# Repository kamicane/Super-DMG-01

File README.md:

# Super DMG-01

A [KiCad](https://www.kicad.org/) 6.0 recreation of the original Game Boy, with a few modern twists.

One of the main goals of this project is to build an entire DMG using only a DMG CPU or a SGB CPU.

## Credits

- bit9 for the [DMG schematics](https://imgur.com/a/X5qKI) and [board scans](https://chipmusic.org/forums/post/215957/#p215957)
- [Gekkio](https://github.com/Gekkio) for the CPU, RAM, CART symbols from [Gekkio KiCad libs](https://github.com/Gekkio/gekkio-kicad-libs)
- [Wesk](https://bitbuilt.net/forums/index.php?members/wesk.1486/) for [these amazing DMG shell scans](https://bitbuilt.net/forums/index.php?threads/dmg-gameboy-scan.4479/), which allow me to do all sort of adapters and covers and whatnot, and test the pcb fitment virtually

## Boards

Like an original DMG, the Super DMG-01 is made out of separate boards. Doumentation for each board can be found in the relative sub-folders:

- CPU Board: [Super DMG CPU](super-dmg-cpu)
- JACK Board: [Super DMG JACK](super-dmg-jack)

## 3rd party boards

To complete the game boy additional boards are required:

- DC CONV Board: use [MouseBiteLabs](https://github.com/MouseBiteLabs)' [DMGC-PWR-01](https://github.com/MouseBiteLabs/Game-Boy-DMG-Color/tree/main/DMGC-PWR-01) or use one from a DMG
- LCD Board: Use any of the available IPS kits or use one from a DMG

## Disclaimer

I am not an electronics expert. Super DMG-01 might fry your games, set your house on fire and kill your pets.

## License

This work is licensed under the [Creative Commons Attribution-ShareAlike 4.0 International License.](http://creativecommons.org/licenses/by-sa/4.0/)

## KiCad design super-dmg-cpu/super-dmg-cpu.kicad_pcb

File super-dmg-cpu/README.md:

# Super DMG CPU

Super DMG CPU works with both IPS and DOT MATRIX LCD boards.

## Credits

The schematic is largely based on [the work done by bit 9](https://imgur.com/a/X5qKI).

I used [Gekkio KiCAD libs](https://github.com/Gekkio/gekkio-kicad-libs) for a few symbols (cpu, ram, cart connector, link port). The specialized footprints were traced by me using fusion 360, using these [scans by bit 9](https://chipmusic.org/forums/topic/13608/dmg-main-board-schematic-circuit-arduinoboy/) as a reference.

## Warning

v1.8 and below have an error with the Link Port, where the footprint was flipped (sigh). If you have a v1.8 or below please don't use the link port, as it might damage the other Game Boy! This was fixed in later versions.

## Features

### Compatibility

Super DMG CPU can be built using new components, except for the CPU, power switch and link connector. It is also possible to use some components harvested from a DMG.

### USB Type-C

The round power connector is replaced with an USB Type-C port. The port is only connected to a pad on the motherboard, you need to add your own battery charger and/or power regulator if you want to make use of it. This port is optional.

### Power distribution IC

A power distribution IC takes the system load away from the power switch, so the game boy remains fully operational even if the switch is not in an optimal condition. This circuit can be bypassed with a jumper.

### Internal ProSound

The headphone output does not pass through the amplifier, only the volume potentiometer.

## BOM

| Designator | Package | Qty | Value / Description | Source |
|------------|---------|-----|---------------------|--------|
| U1 | QFP-80 14x20 p0.8 | 1 | CPU | DMG, SGB
| U2 | SOP-28 17.5x8.4 p1.27 | 1 | VRAM | DMG, SGB, [LCSC](https://lcsc.com/product-detail/C1351073.html)
| U3 | SOP-28 17.5x8.4 p1.27 | 1 | RAM | DMG, SGB, [LCSC](https://lcsc.com/product-detail/C1351073.html)
| U4 | SSOP-18 6x7.4 p0.8 | 1 | Audio Amplifier | DMG
| EXT1 | | 1 | Link Connector | DMG
| DA1, DA2, DA3, DA4 | SOT-23-3 | 4 | BAV99-7-F | [LCSC](https://www.lcsc.com/product-detail/C106919.html)
| C1, C23 | 3528 | 2 | 100µf tantalum | [LCSC](https://lcsc.com/product-detail/C122271.html)
| SW1 | | 1 | Power Switch | DMG
| U5 | SOT-23-5 | 1 | Power Distribution | [LCSC](https://lcsc.com/product-detail/C517266.html)
| D2 | SOD-123 | 1 | 1N414 | [LCSC](https://lcsc.com/product-detail/C83528.html)
| X1 | HC-49S | 1 | 4.194304 MHz | DMG, [LCSC (TH)](https://lcsc.com/product-detail/C718646.html), [LCSC (SMD)](https://lcsc.com/product-detail/C2149317.html)
| USB1 | USB_C_16p | 1 | Charge Connector | [LCSC](https://lcsc.com/product-detail/C2931472.html)
| VR1 | | 1 | Volume Pot | DMG, [AliExpress](https://www.aliexpress.com/item/32840044311.html)
| CN1 | 1.25 x 21 SMD | 1 | LCD Board Connector | DMG, [AliExpress](https://www.aliexpress.com/item/1005005484837763.html)
| CN2 |  | 1 | Cart Connector | DMG, [AliExpress](https://www.aliexpress.com/item/1005002719771295.html)
| CN3 | | 1 | AA Battery Contacts | DMG, [AliExpress](https://www.aliexpress.com/item/32801068366.html)
| CN4 | 1.25 TH | 1 | Lipo Battery Connector | [LCSC](https://www.lcsc.com/product-detail/C722595.html)
| C3, C4 | 0805 | 2 | 1µF |
| C5, C6 | 0805 | 2 | 10µF |
| C7, C8, C9 | 0805 | 3 | 47nF |
| C10, C24, C25 | 0805 | 3 | 100nF |
| C12, C13, C14 | 0805 | 3 | 10nF |
| C16, C17, C18, C19 | 0805| 4 | 100pF |
| C21, C22 | 0805 | 2 | 27pF |
| R1, R2, R3, R4 | 0805 | 4 | 220Ω|
| R5, R6 | 0805 | 2 | 510Ω |
| R7 | 0805 | 1 | 180kΩ |
| R8 | 0805 | 1 | 1MΩ |
| R9 | 0805 | 1 | 10kΩ |
| R10, R11 | 0805 | 2 | 5.1kΩ |

## Assembly

- Solder all SMD components on the front side
- If using a power board with integrated power distribution close ```J5``` and do not install ```U5```, ```C24```, ```C25```, ```R9```
- If using an external amplifier, such as [Super DMG JACK](../super-dmg-jack) do not install ```U4```, ```C5-C9```, ```C23```
- If you do not need link functionality you can omit ```EXT1```, ```DA1-DA4```, ```R1-R4```, ```C16-C19```, ```D2```
- Solder the through hole components and the LCD board connector
- (Optional) solder the usb connector and cut an opening for the usb port in the front shell using the provided [rudimentary jig](../3d_models/dmg_usbc_jig.stl)
- The original DC jack hole can be covered with this simple [3d printed plug](../3d_models/dmg_dc_plug.stl)

## Notes

If using an original LCD board you need an original *DMG DC CONV* voltage regulator, as acceptable modern replacements that also include the -18v rail *do not exist yet*.

This pcb cannot be easily biverted yet.

## Ordering

Make sure you order with 1.0mm thickness.

## License

This work is licensed under the [Creative Commons Attribution-ShareAlike 4.0 International License.](http://creativecommons.org/licenses/by-sa/4.0/)

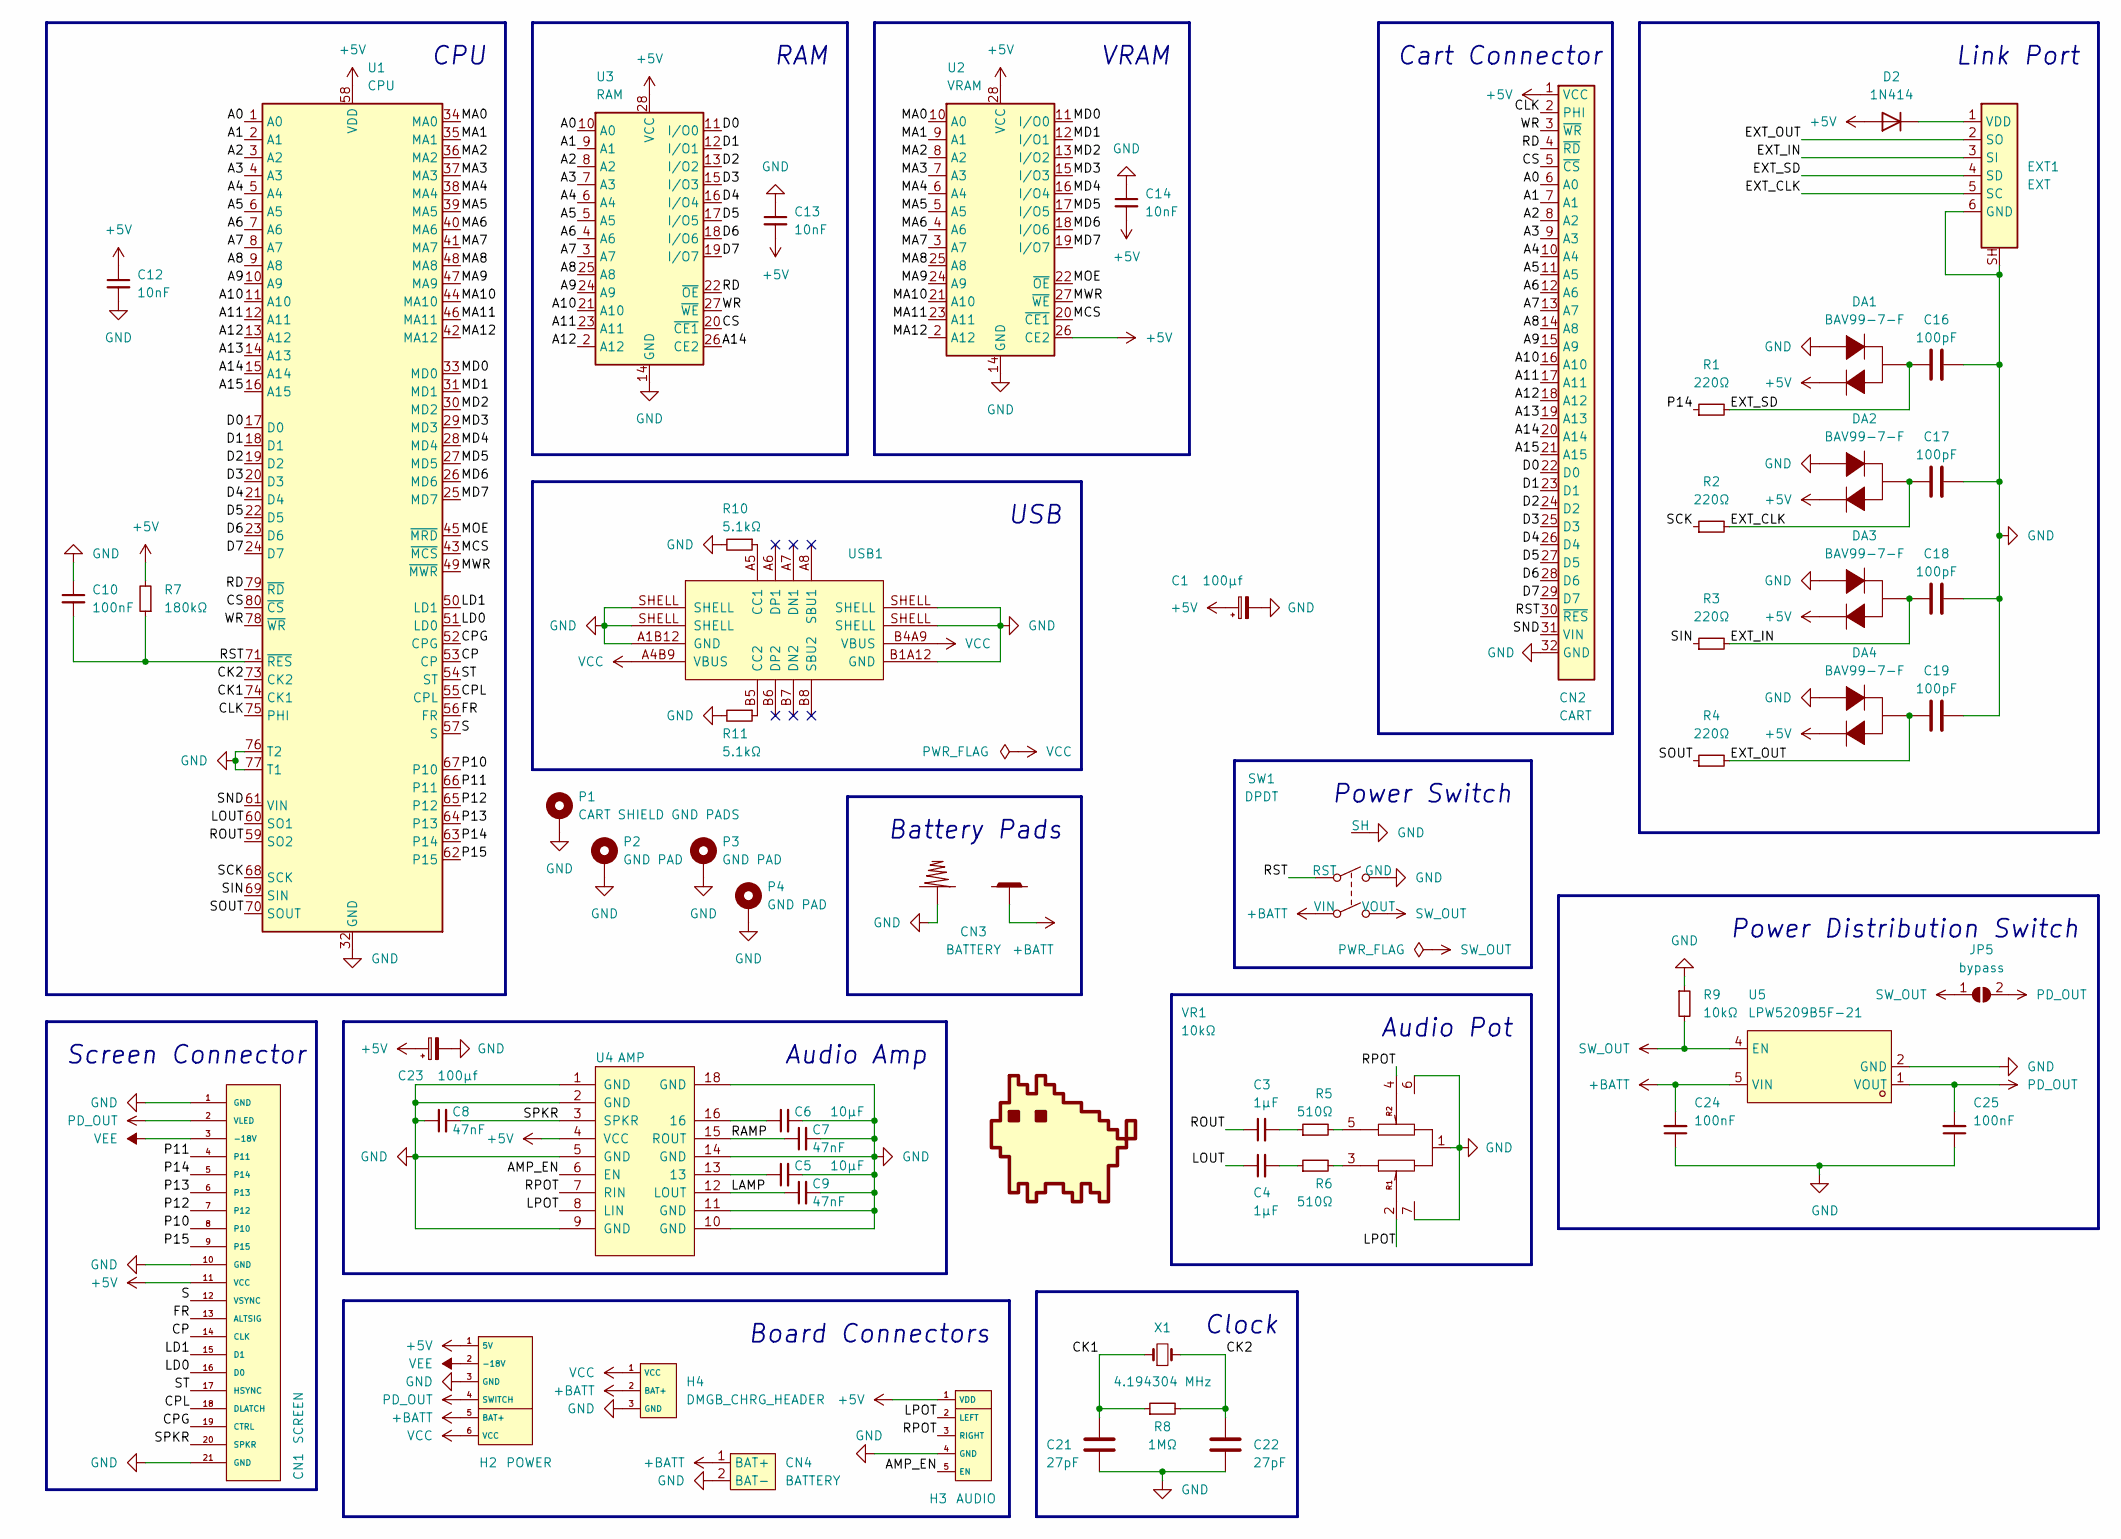
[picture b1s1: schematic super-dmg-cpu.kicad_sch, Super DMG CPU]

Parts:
C1, C23: 100µf; CP_EIA-3528-12_Kemet-T_Pad1.50x2.35mm_HandSolder; LCSC C122271
C3, C4: 1µF; C_0805_2012Metric_Pad1.18x1.45mm_HandSolder; LCSC C28323
C5, C6: 10µF; C_0805_2012Metric_Pad1.18x1.45mm_HandSolder; LCSC C15850
C7, C8, C9: 47nF; C_0805_2012Metric_Pad1.18x1.45mm_HandSolder; LCSC C53134
C10, C24, C25: 100nF; C_0805_2012Metric_Pad1.18x1.45mm_HandSolder; LCSC C49678
C12, C13, C14: 10nF; C_0805_2012Metric_Pad1.18x1.45mm_HandSolder; LCSC C1710
C16, C17, C18, C19: 100pF; C_0805_2012Metric_Pad1.18x1.45mm_HandSolder; LCSC C1790
C21, C22: 27pF; C_0805_2012Metric_Pad1.18x1.45mm_HandSolder; LCSC C527182
CN1: SCREEN; DMG_FPC_CONN
CN2: CART; DMG_CART_CONN
CN3: BATTERY; DMG_BATTERY_PADS
CN4: BATTERY; CONN-TH_2P-P1.25_HCTL_HC-1.25-2AW; LCSC C2845535
D2: 1N414; D_SOD-123; LCSC C83528
DA1, DA2, DA3, DA4: BAV99-7-F; SOT-23-3_L2.9-W1.3-P1.90-LS2.4-BR; LCSC C106919
EXT1: EXT; DMG_LINK_CONN
G1: kmc; kmc_6mm
H2: POWER; PAD_2.54_HYBRID_X6
H3: AUDIO; PAD_2.54_HYBRID_X5
H4: DMGB_CHRG_HEADER; PAD_2.54_HYBRID_X3
JP5: bypass; solder_jumper_x2
P1: CART SHIELD GND PADS; DMG_CART_SHIELD_CONTACT
P2, P3, P4: GND PAD; DMG_GROUNDPAD
R1, R2, R3, R4: 220Ω; R_0805_2012Metric_Pad1.20x1.40mm_HandSolder; LCSC C17557
R5, R6: 510Ω; R_0805_2012Metric_Pad1.20x1.40mm_HandSolder; LCSC C17734
R7: 180kΩ; R_0805_2012Metric_Pad1.20x1.40mm_HandSolder; LCSC C17501
R8: 1MΩ; R_0805_2012Metric_Pad1.20x1.40mm_HandSolder; LCSC C17514
R9: 10kΩ; R_0805_2012Metric_Pad1.20x1.40mm_HandSolder; LCSC C17414
R10, R11: 5.1kΩ; R_0805_2012Metric_Pad1.20x1.40mm_HandSolder; LCSC C27834
SW1: DPDT; DMGB_POWER_SWITCH; LCSC C2848866
U1: CPU; DMG_CPU
U2: VRAM; DMG_RAM_64K
U3: RAM; DMG_RAM_64K
U4: AMP; DMG_AMP
U5: LPW5209B5F-21; SOT-23-5_L2.9-W1.6-P0.95-LS2.8-BL; JLC Part Extended Part
USB1: CHARGE_PORT; USB_C_16p; LCSC C319148
VR1: 10kΩ; DMG_VOLUME_POT
X1: 4.194304 MHz; HC-49S; LCSC C2149317

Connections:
+5V: C1.1, C12.1, C13.2, C14.2, C23.1, CN1.11 (VCC), CN2.1 (VCC), D2.2 (A), DA1.2 (K), DA2.2 (K), DA3.2 (K), DA4.2 (K), H2.1 (5V), H3.1 (VDD), R7.2, U1.58 (VDD), U2.26 (CE2), U2.28 (VCC), U3.28 (VCC), U4.4 (VCC)
+BATT: C24.2, CN3.1 (+), CN4.1 (BAT+), H2.5 (BAT+), H4.2 (BAT+), SW1.2 (VIN), U5.5 (VIN)
/A0: CN2.6 (A0), U1.1 (A0), U3.10 (A0)
/A1: CN2.7 (A1), U1.2 (A1), U3.9 (A1)
/A2: CN2.8 (A2), U1.3 (A2), U3.8 (A2)
/A3: CN2.9 (A3), U1.4 (A3), U3.7 (A3)
/A4: CN2.10 (A4), U1.5 (A4), U3.6 (A4)
/A5: CN2.11 (A5), U1.6 (A5), U3.5 (A5)
/A6: CN2.12 (A6), U1.7 (A6), U3.4 (A6)
/A7: CN2.13 (A7), U1.8 (A7), U3.3 (A7)
/A8: CN2.14 (A8), U1.9 (A8), U3.25 (A8)
/A9: CN2.15 (A9), U1.10 (A9), U3.24 (A9)
/A10: CN2.16 (A10), U1.11 (A10), U3.21 (A10)
/A11: CN2.17 (A11), U1.12 (A11), U3.23 (A11)
/A12: CN2.18 (A12), U1.13 (A12), U3.2 (A12)
/A13: CN2.19 (A13), U1.14 (A13)
/A14: CN2.20 (A14), U1.15 (A14), U3.26 (CE2)
/A15: CN2.21 (A15), U1.16 (A15)
/AMP_EN: H3.5 (EN), U4.6 (EN)
/CK1: C21.2, R8.1, U1.74 (CK1), X1.1
/CK2: C22.2, R8.2, U1.73 (CK2), X1.2
/CLK: CN2.2 (PHI), U1.75 (PHI)
/CP: CN1.14 (CLK), U1.53 (CP)
/CPG: CN1.19 (CTRL), U1.52 (CPG)
/CPL: CN1.18 (DLATCH), U1.55 (CPL)
/CS: CN2.5 (~CS), U1.80 (~CS), U3.20 (~CE1)
/D0: CN2.22 (D0), U1.17 (D0), U3.11 (I/O0)
/D1: CN2.23 (D1), U1.18 (D1), U3.12 (I/O1)
/D2: CN2.24 (D2), U1.19 (D2), U3.13 (I/O2)
/D3: CN2.25 (D3), U1.20 (D3), U3.15 (I/O3)
/D4: CN2.26 (D4), U1.21 (D4), U3.16 (I/O4)
/D5: CN2.27 (D5), U1.22 (D5), U3.17 (I/O5)
/D6: CN2.28 (D6), U1.23 (D6), U3.18 (I/O6)
/D7: CN2.29 (D7), U1.24 (D7), U3.19 (I/O7)
/EXT_CLK: C17.1, DA2.3 (K), EXT1.5 (SC), R2.2
/EXT_IN: C18.1, DA3.3 (K), EXT1.3 (SI), R3.2
/EXT_OUT: C19.1, DA4.3 (K), EXT1.2 (SO), R4.2
/EXT_SD: C16.1, DA1.3 (K), EXT1.4 (SD), R1.2
/FR: CN1.13 (ALTSIG), U1.56 (FR)
/LAMP: C9.1, U4.12 (LOUT)
/LD0: CN1.16 (D0), U1.51 (LD0)
/LD1: CN1.15 (D1), U1.50 (LD1)
/LOUT: C4.1, U1.60 (SO1)
/LPOT: H3.2 (LEFT), U4.8 (LIN), VR1.2
/MA0: U1.34 (MA0), U2.10 (A0)
/MA1: U1.35 (MA1), U2.9 (A1)
/MA2: U1.36 (MA2), U2.8 (A2)
/MA3: U1.37 (MA3), U2.7 (A3)
/MA4: U1.38 (MA4), U2.6 (A4)
/MA5: U1.39 (MA5), U2.5 (A5)
/MA6: U1.40 (MA6), U2.4 (A6)
/MA7: U1.41 (MA7), U2.3 (A7)
/MA8: U1.48 (MA8), U2.25 (A8)
/MA9: U1.47 (MA9), U2.24 (A9)
/MA10: U1.44 (MA10), U2.21 (A10)
/MA11: U1.46 (MA11), U2.23 (A11)
/MA12: U1.42 (MA12), U2.2 (A12)
/MCS: U1.43 (~MCS), U2.20 (~CE1)
/MD0: U1.33 (MD0), U2.11 (I/O0)
/MD1: U1.31 (MD1), U2.12 (I/O1)
/MD2: U1.30 (MD2), U2.13 (I/O2)
/MD3: U1.29 (MD3), U2.15 (I/O3)
/MD4: U1.28 (MD4), U2.16 (I/O4)
/MD5: U1.27 (MD5), U2.17 (I/O5)
/MD6: U1.26 (MD6), U2.18 (I/O6)
/MD7: U1.25 (MD7), U2.19 (I/O7)
/MOE: U1.45 (~MRD), U2.22 (~OE)
/MWR: U1.49 (~MWR), U2.27 (~WE)
/P10: CN1.8 (P10), U1.67 (P10)
/P11: CN1.4 (P11), U1.66 (P11)
/P12: CN1.7 (P12), U1.65 (P12)
/P13: CN1.6 (P13), U1.64 (P13)
/P14: CN1.5 (P14), R1.1, U1.63 (P14)
/P15: CN1.9 (P15), U1.62 (P15)
/RAMP: C7.1, U4.15 (ROUT)
/RD: CN2.4 (~RD), U1.79 (~RD), U3.22 (~OE)
/ROUT: C3.1, U1.59 (SO2)
/RPOT: H3.3 (RIGHT), U4.7 (RIN), VR1.4
/RST: C10.2, CN2.30 (~RES), R7.1, SW1.5 (RST), U1.71 (~RES)
/S: CN1.12 (VSYNC), U1.57 (S)
/SCK: R2.1, U1.68 (SCK)
/SIN: R3.1, U1.69 (SIN)
/SND: CN2.31 (VIN), U1.61 (VIN)
/SOUT: R4.1, U1.70 (SOUT)
/SPKR: C8.2, CN1.20 (SPKR), U4.3 (SPKR)
/ST: CN1.17 (HSYNC), U1.54 (ST)
/WR: CN2.3 (~WR), U1.78 (~WR), U3.27 (~WE)
GND: C1.2, C5.2, C6.2, C7.2, C8.1, C9.2, C10.1, C12.2, C13.1, C14.1, C16.2, C17.2, C18.2, C19.2, C21.1, C22.1, C23.2, C24.1, C25.1, CN1.1 (GND), CN1.10 (GND), CN1.21 (GND), CN2.32 (GND), CN3.2 (-), CN4.2 (BAT-), DA1.1 (A), DA2.1 (A), DA3.1 (A), DA4.1 (A), EXT1.6 (GND), EXT1.SH, H2.3 (GND), H3.4 (GND), H4.3 (GND), P1.1, P2.1, P3.1, P4.1, R9.1, R10.2, R11.2, SW1.6 (GND), SW1.7 (SH), U1.32 (GND), U1.72 (GND), U1.76 (T2), U1.77 (T1), U2.14 (GND), U3.14 (GND), U4.1 (GND), U4.2 (GND), U4.5 (GND), U4.9 (GND), U4.10 (GND), U4.11 (GND), U4.14 (GND), U4.18 (GND), U5.2 (GND), USB1.A1B12 (GND), USB1.B1A12 (GND), USB1.SHELL, VR1.1, VR1.6 (EH), VR1.7 (EH)
unnamed: C3.2, R5.1
unnamed: C4.2, R6.1
unnamed: C5.1, U4.13
unnamed: C6.1, U4.16
unnamed: D2.1 (K), EXT1.1 (VDD)
unnamed: R5.2, VR1.5
unnamed: R6.2, VR1.3
unnamed: R10.1, USB1.A5 (CC1)
unnamed: R11.1, USB1.B5 (CC2)
PD_OUT: C25.2, CN1.2 (VLED), H2.4 (SWITCH), JP5.2 (B), U5.1 (VOUT)
SW_OUT: JP5.1 (A), R9.2, SW1.1 (VOUT), U5.4 (EN)
VCC: H2.6 (VCC), H4.1 (VCC), USB1.A4B9 (VBUS), USB1.B4A9 (VBUS)
VEE: CN1.3 (-18V), H2.2 (-18V)

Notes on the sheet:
USB
VRAM
Clock
Board Connectors
Power Switch
Battery Pads
Audio Amp
Link Port
Cart Connector
RAM
CPU
Audio Pot
Power Distribution Switch
Screen Connector

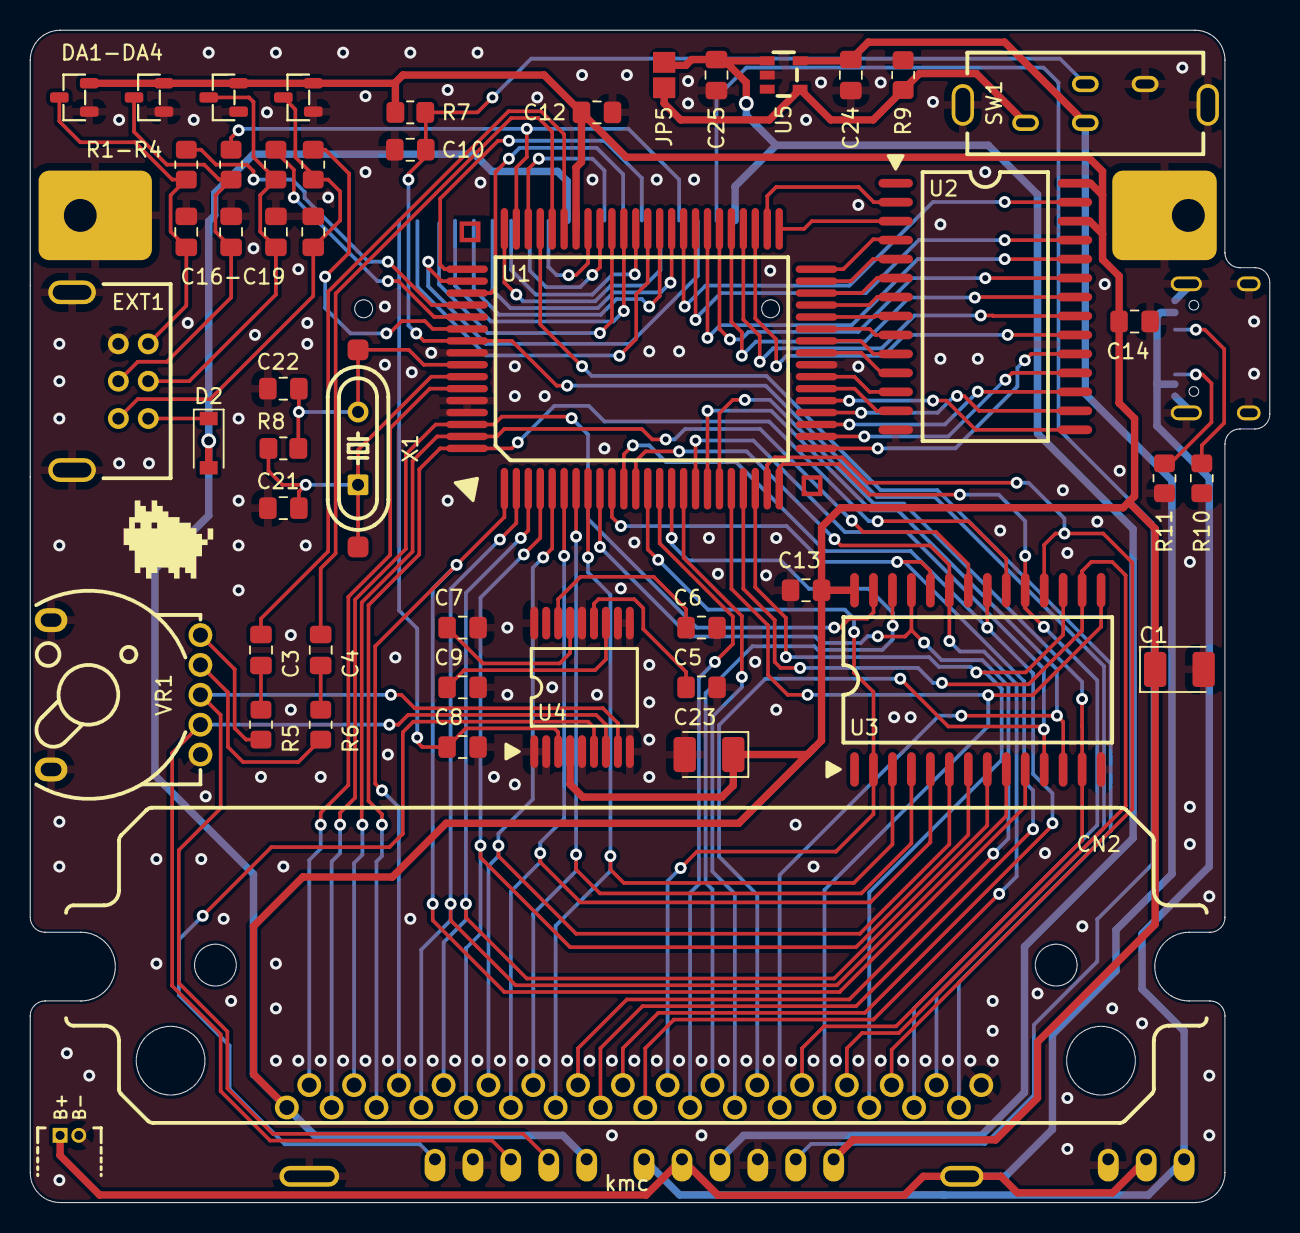
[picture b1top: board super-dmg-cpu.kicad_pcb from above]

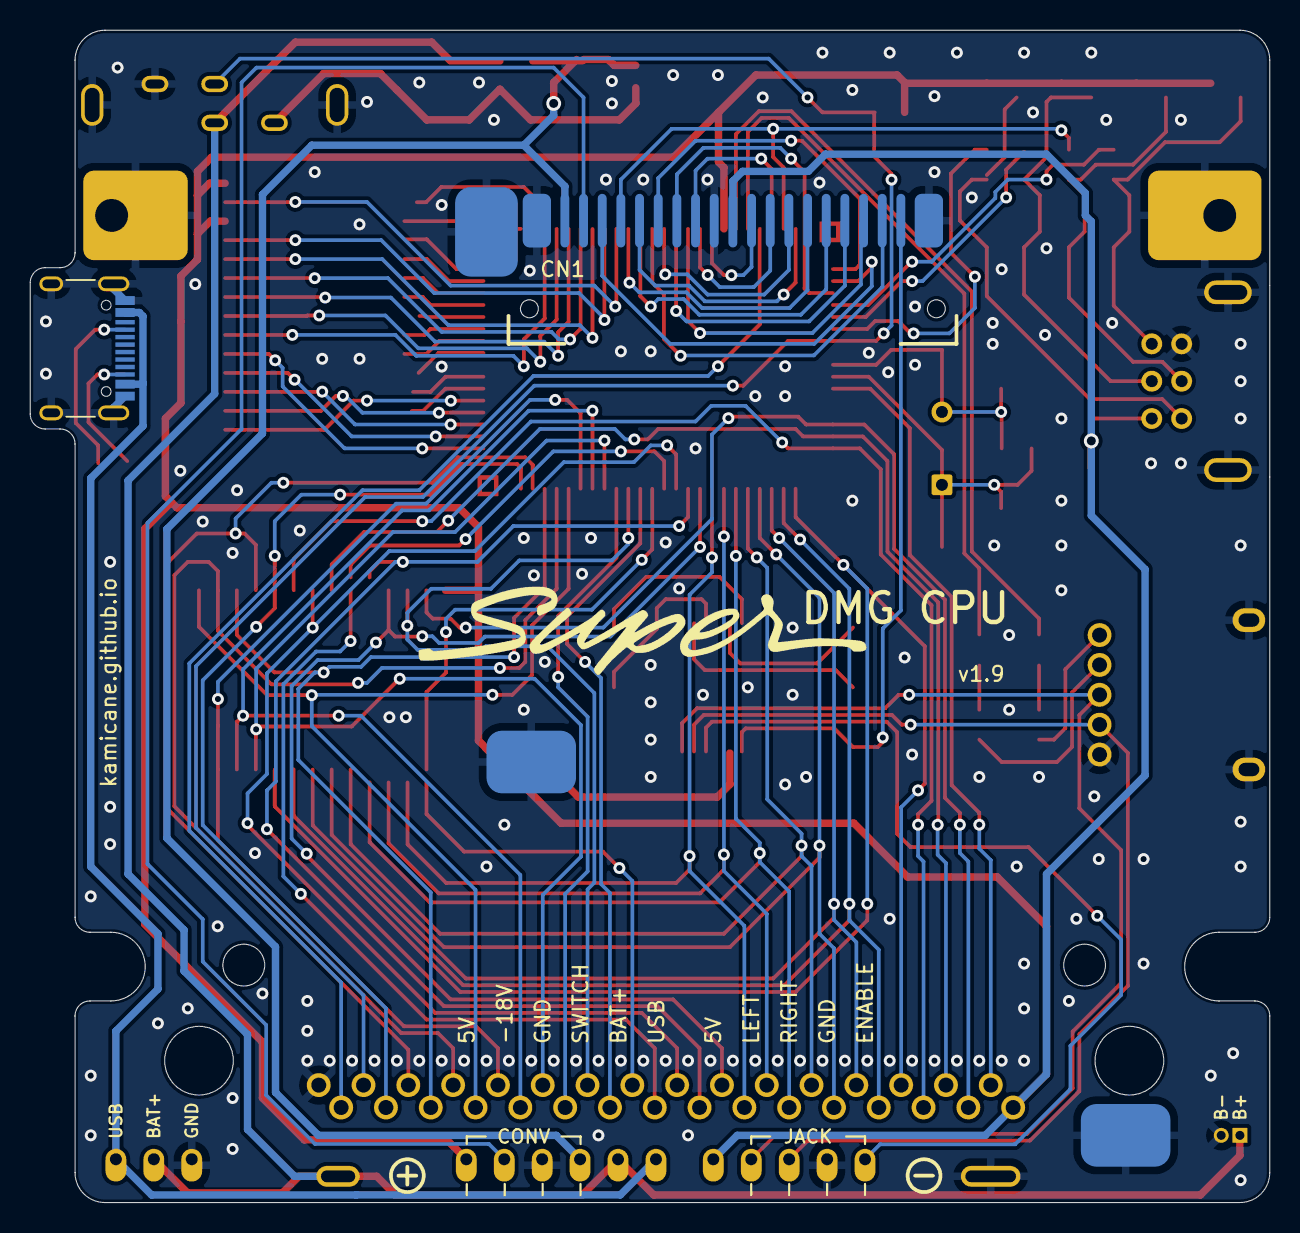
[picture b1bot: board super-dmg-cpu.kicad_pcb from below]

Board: 2 copper layers, 83.0 x 78.5 mm, 60 parts (8 on the bottom side), 101 nets.

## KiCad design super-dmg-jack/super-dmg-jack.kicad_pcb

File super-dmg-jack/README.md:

# Super DMG JACK

Super DMG JACK is a replacement headphone/audio PCB for the original Game Boy. It can be used on a stock DMG or the Super DMG-01.

It uses a PAM8302 mono amplifier to power the speaker when no headphones are present, but it can also be built as a headphone jack replacement using the amplifier on the CPU board.

The amplifier schematic is based on [Adafruit's pam8302 amplifier PCB](https://github.com/adafruit/Adafruit-PAM8302-Mono-Amplifier-PCB).

The headphone output needs to be unamplified, and grabbed _after_ the DMG volume potentiometer.

## BOM

| Designator | Package | Qty | Value / Description | Source |
|------------|---------|-----|---------------------|--------|
| CN1 | PJ-3043-B | 1 | Headphone connector | [LCSC](https://lcsc.com/product-detail/C2682182.html) |
| CN2 | 1.25 TH | 1 | CPU PCB Connector | [LCSC](https://lcsc.com/product-detail/C722595.html) |
| CN3 | 1.25 TH | 1 | Speaker Connector | [LCSC](https://lcsc.com/product-detail/C722604.html) |
| U1 | SOP-8 | 1 | PAM8302 | [LCSC](https://lcsc.com/product-detail/C112137.html) |
| U2 | SOT-23-5 | 1 | SN74AHC1G14 | [LCSC](https://lcsc.com/product-detail/C7469.html) |
| VR1 | Bourns TC33X-2-103E | 1 | 10kΩ SMD | [LCSC](https://lcsc.com/product-detail/C719176.html) |
| FB1, FB2 | 0805 | 2 | Ferrite Bead ||
| C1, C2, C5 | 0805 | 3 | 1µf ||
| C3, C4 | 0805 | 3 | 220pf ||
| R1, R2 | 0805 | 2 | 220Ω ||
| R3, R4 | 0805 | 2 | 100Ω ||
| R5 | 0805 | 1 | 10kΩ ||

I got premade wires from [AliExpress](https://www.aliexpress.com/item/1005002353691025.html) (1.25mm 2p and 5p), but you can also just use 28/30 awg without connectors.

I use "WSC" 8Ω 2W speakers from AliExpress.

## DMG Pinout

## Full Installation

Important: do not solder ```U2``` and/or do not wire the (E)nable signal. The speaker must be connected to this board.

- Solder the SMD components
- Solder the through hole components
- On the stock DMG solder the L/R signals to the volume potentiometer (** after pot), on Super DMG-01 solder to the bottom pads directly
- Get power from the 5v rail on the CPU board
- Adjust the trimpot

### Trimpot notes

Adjust the trimpot to reduce the power draw and max volume of the amplifier. Boot the DMG at minimum volume, and slowly turn it up, while also adjusting the trimpot. The Game Boy will shut down if you're drawing too much power.
Do the final trimpot adjustment once the DMG volume is at its maximum value.

The final maximum volume will depend on the batteries and the voltage regulator you're using.

## Jack-only Installation

The jack-only installation is meant to be used with the on-board DMG amplifier, however you still need to solder an extra wire for power as the ENABLE signal needs to be inverted.

Important: solder only ```U2```, ```R5```, the headphone jack and the CPU PCB connector. The speaker must be kept in the LCD board.

- Solder the SMD components
- Solder the through hole components
- On the stock DMG solder the L/R signals to the volume potentiometer (** after pot), on Super DMG-01 solder to the bottom pads directly
- Get power from 5V (Super DMG CPU) or SW (stock DMG) on the CPU board

## Notes

3d print the [jack spacer](../3d_models/super_dmg_jack_spacer.stl) for correct alignment.

## Ordering

Make sure you order in 1.0mm thickness.

## License

This work is licensed under the [Creative Commons Attribution-ShareAlike 4.0 International License.](http://creativecommons.org/licenses/by-sa/4.0/)

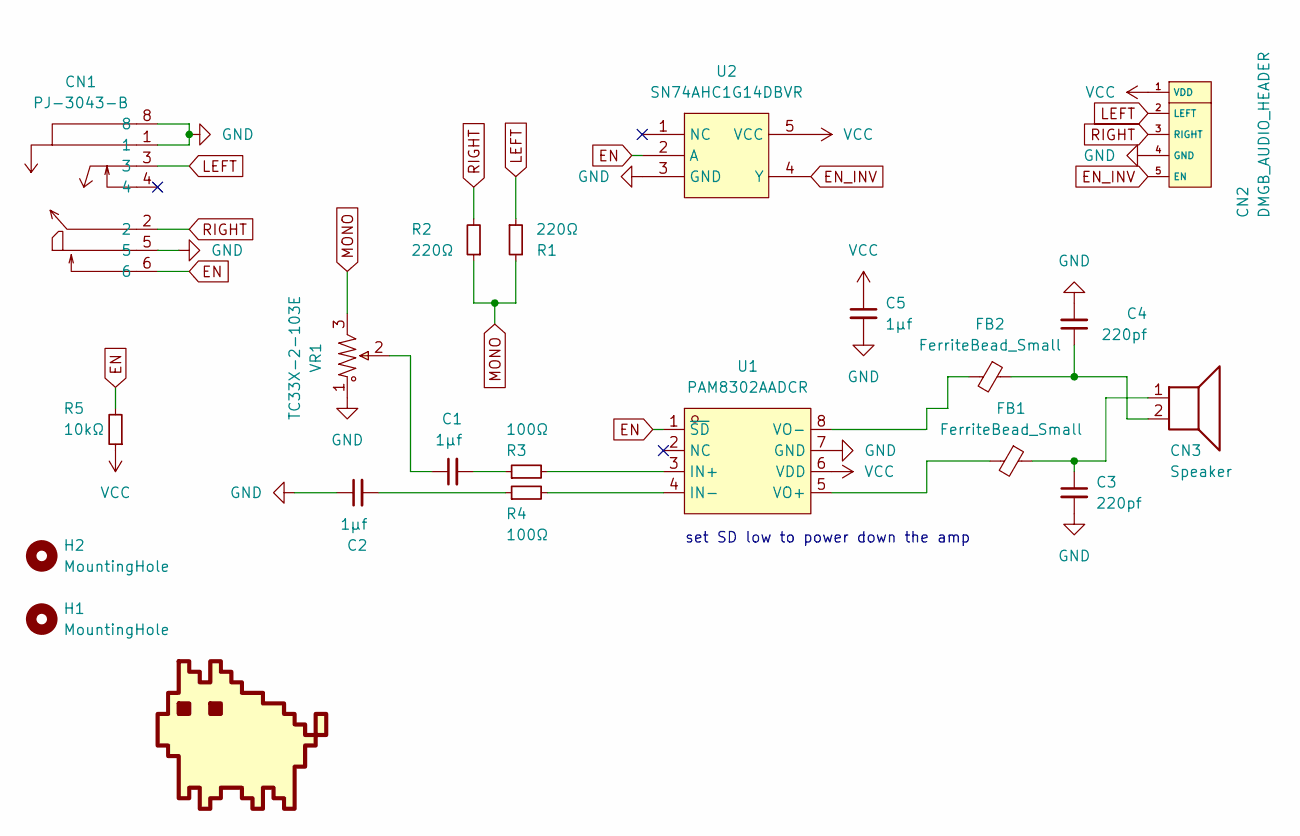
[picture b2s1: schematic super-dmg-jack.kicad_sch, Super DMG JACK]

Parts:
C1, C2, C5: 1µf; C_0805_2012Metric_Pad1.18x1.45mm_HandSolder
C3, C4: 220pf; C_0805_2012Metric_Pad1.18x1.45mm_HandSolder
CN1: PJ-3043-B; AUDIO-TH_PJ-3043-B; LCSC C2682182
CN2: DMGB_AUDIO_HEADER; CONN-TH_5P-P1.25_LONGPADS; LCSC C722604
CN3: Speaker; CONN-TH_2P-P1.25_HCTL_HC-1.25-2AW_LONGPADS; LCSC C722595
FB1, FB2: FerriteBead_Small; L_0805_2012Metric_Pad1.15x1.40mm_HandSolder
G1: kmc
H1, H2: MountingHole; MountingHole_2.2mm_M2
R1, R2: 220Ω; R_0805_2012Metric_Pad1.20x1.40mm_HandSolder
R3, R4: 100Ω; R_0805_2012Metric_Pad1.20x1.40mm_HandSolder
R5: 10kΩ; R_0805_2012Metric_Pad1.20x1.40mm_HandSolder
U1: PAM8302AADCR; SOP-8_L4.9-W3.9-P1.27-LS6.0-BL; LCSC C112137
U2: SN74AHC1G14DBVR; SOT-23-5_L3.0-W1.7-P0.95-LS2.8-BR; LCSC C7469
VR1: TC33X-2-103E; RES-ADJ-SMD_3P-L3.0-W3.8-P1.75-BR; LCSC C719176

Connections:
EN: CN1.6, R5.2, U1.1 (~SD), U2.2 (A)
EN_INV: CN2.5 (EN), U2.4 (Y)
GND: C2.1, C3.2, C4.2, C5.2, CN1.1, CN1.5, CN1.8, CN2.4 (GND), U1.7 (GND), U2.3 (GND), VR1.1
LEFT: CN1.3, CN2.2 (LEFT), R1.1
MONO: R1.2, R2.1, VR1.3
unnamed: C1.1, VR1.2
unnamed: C1.2, R3.1
unnamed: C2.2, R4.1
unnamed: C3.1, CN3.1, FB1.1
unnamed: C4.1, CN3.2, FB2.1
unnamed: FB1.2, U1.5 (VO+)
unnamed: FB2.2, U1.8 (VO-)
unnamed: R3.2, U1.3 (IN+)
unnamed: R4.2, U1.4 (IN-)
RIGHT: CN1.2, CN2.3 (RIGHT), R2.2
VCC: C5.1, CN2.1 (VDD), R5.1, U1.6 (VDD), U2.5 (VCC)

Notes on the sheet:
set SD low to power down the amp

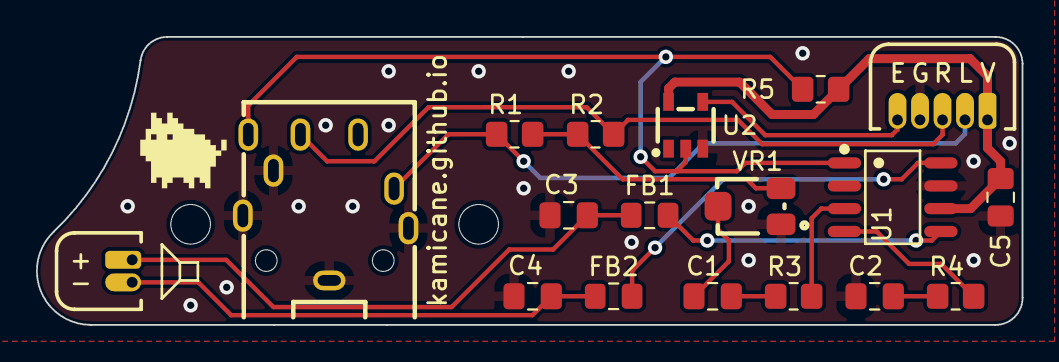
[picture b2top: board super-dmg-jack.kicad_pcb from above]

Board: 2 copper layers, 54.8 x 16.0 mm, 21 parts (0 on the bottom side), 16 nets.

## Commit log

2022-10-04 add images
2022-10-05 removed kicad_prl
2022-11-27 - fix c23 orientation - fix d2 footprint - minor silkscreen changes
2022-11-27 remove extra power distribution switch capacitors since they were not needed
2022-11-28 update images
2022-11-28 remove unused SPKR pad clean up bottom area add optional jst style connectors
2022-12-01 test connectors (for history, to be removed)
2022-12-02 fixed battery connector (!) less stupid routing in some areas minor changes
2022-12-02 pass DRC with roundtracks at 0.6
2022-12-02 add basic BOM with LCSC parts
2022-12-02 README, add pcbdraw style, update images
2022-12-02 README, images
2022-12-03 significantly simplified the power stuff
2022-12-03 v1.5
2022-12-03 fix wrong back image
2022-12-03 ignore autogenerated rounded board
2022-12-03 minor tracks cleanup
2022-12-05 change side of 5v pin on the audio header
2022-12-06 more pedantic changes
2022-12-07 fix link
2022-12-15 better bottom pads
    - more clearance between the battery terminals and bottom pads
    - swapped +bat and usb on the power pads because it makes more sense
    - marked more clearly where the og boards go
    - small routing optimizations
    - small cosmetic changes
2023-01-04 Version 1.7 - Rebranding - Fix AA negative battery contact - Add charger pads - Made the power switch footprint compatible with a 3rd party switch - Add experimental JACK board - PCBWaaaaaaaaaaaaaaaa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
2023-01-04 sub-boards clarification
2023-01-09 remove link to incompatible power switch :(
2023-01-16 Jack: README, prepare for release - images - minor cosmetic changes
2023-01-16 CPU: fix inverted L/R pins
2023-01-16 JACK: engrish, trimpot note
2023-01-16 CPU: remove unused pads on the power switch
2023-01-16 CPU: clean up for DRC
2023-01-16 JACK: clean up for DRC
2023-01-16 jack: add pcbway links
2023-01-16 CPU: update pcb 2d images
2023-11-16 Fixed the link port - The link port footprint was flipped
2023-11-16 note about the link port error in cpu/README
2023-11-16 finished preliminary update to kicad 7
2023-11-17 preparing for gerbers release
2023-11-17 v1.9
2024-04-16 alternative lcd board connector
